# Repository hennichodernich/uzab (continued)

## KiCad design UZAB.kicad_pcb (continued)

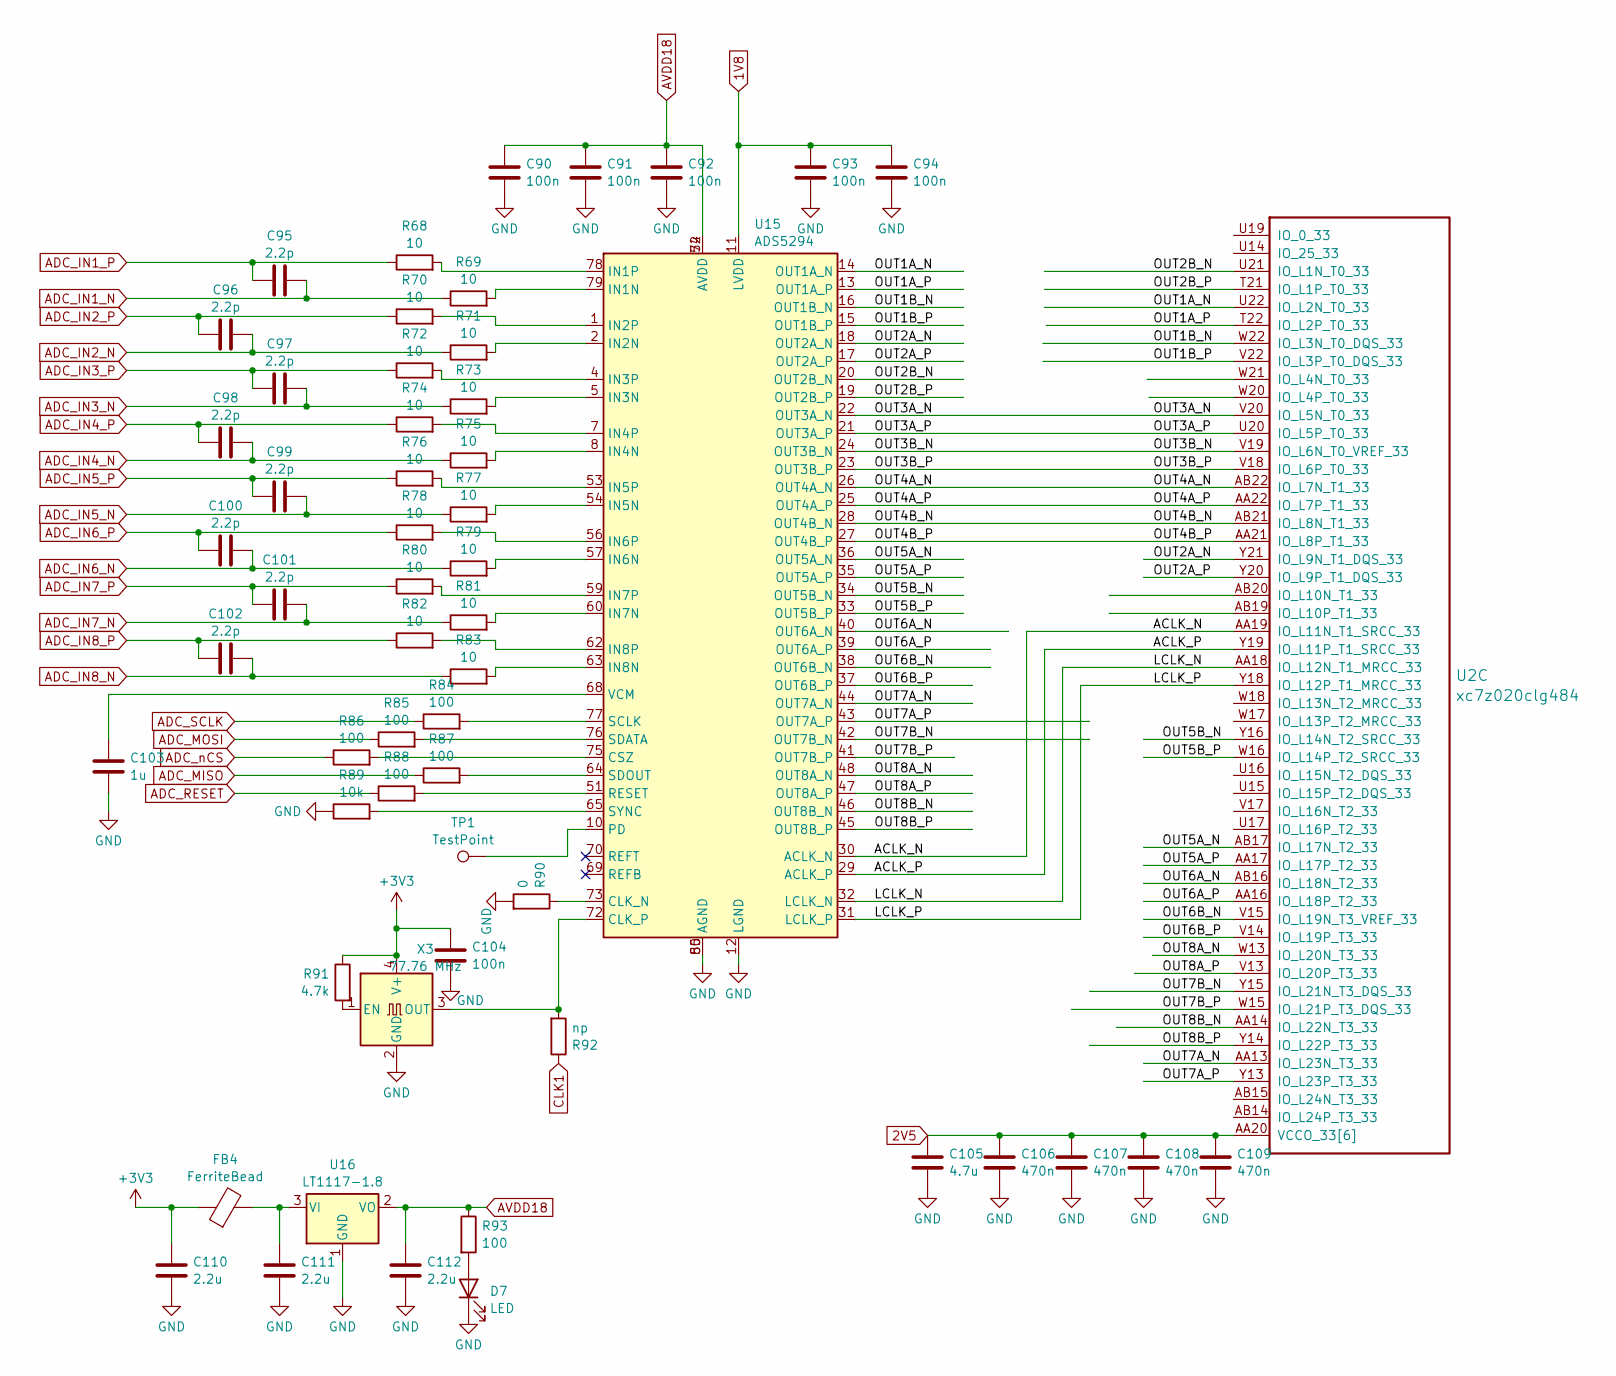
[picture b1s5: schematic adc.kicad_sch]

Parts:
C90, C91, C92, C93, C94, C104: 100n; C_0402_1005Metric
C95, C96, C97, C98, C99, C100, C101, C102: 2.2p; C_0402_1005Metric
C103: 1u; C_0603_1608Metric
C105: 4.7u; C_0603_1608Metric
C106, C107, C108, C109: 470n; C_0201_BGA
C110, C111, C112: 2.2u; C_0603_1608Metric
D7: LED; LED_0603_1608Metric
FB4: FerriteBead; L_0603_1608Metric
R68, R69, R70, R71, R72, R73, R74, R75, R76, R77, R78, R79, R80, R81, R82, R83: 10; R_0402_1005Metric
R84, R85, R86, R87, R88: 100; C_0603_1608Metric
R89: 10k; C_0603_1608Metric
R90: 0; R_0402_1005Metric
R91: 4.7k; R_0402_1005Metric
R92: np; R_0402_1005Metric
R93: 100; R_0603_1608Metric
TP1: TestPoint; TestPoint_Pad_1.0x1.0mm
U2: xc7z020clg484; Xilinx_CLG484_CLG485
U15: ADS5294; HTQFP-80-1EP_12x12mm_P0.5mm_EP10x10mm
U16: LT1117-1.8; SOT-223-3_TabPin2
X3: 77.76 MHz; Oscillator_SMD_EuroQuartz_XO91-4Pin_7.0x5.0mm

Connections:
1V8: C93.1, C94.1, U15.11 (LVDD), U15.49 (LVDD); also elsewhere on the board
2V5: C105.1, C106.1, C107.1, C108.1, C109.1, U2.AA20 (VCCO_33[6]), U2.AB13 (VCCO_33[6]), U2.U18 (VCCO_33[6]), U2.V21 (VCCO_33[6]), U2.W14 (VCCO_33[6]), U2.Y17 (VCCO_33[6]); also elsewhere on the board
3V3: C104.1, C110.1, FB4.1, R91.1, X3.4 (V+); also elsewhere on the board
/ADC/ACLK_N: U2.AA19 (IO_L11N_T1_SRCC_33), U15.30 (ACLK_N)
/ADC/ACLK_P: U2.Y19 (IO_L11P_T1_SRCC_33), U15.29 (ACLK_P)
/ADC/LCLK_N: U2.AA18 (IO_L12N_T1_MRCC_33), U15.32 (LCLK_N)
/ADC/LCLK_P: U2.Y18 (IO_L12P_T1_MRCC_33), U15.31 (LCLK_P)
/ADC/OUT1A_N: U2.U22 (IO_L2N_T0_33), U15.14 (OUT1A_N)
/ADC/OUT1A_P: U2.T22 (IO_L2P_T0_33), U15.13 (OUT1A_P)
/ADC/OUT1B_N: U2.W22 (IO_L3N_T0_DQS_33), U15.16 (OUT1B_N)
/ADC/OUT1B_P: U2.V22 (IO_L3P_T0_DQS_33), U15.15 (OUT1B_P)
/ADC/OUT2A_N: U2.Y21 (IO_L9N_T1_DQS_33), U15.18 (OUT2A_N)
/ADC/OUT2A_P: U2.Y20 (IO_L9P_T1_DQS_33), U15.17 (OUT2A_P)
/ADC/OUT2B_N: U2.U21 (IO_L1N_T0_33), U15.20 (OUT2B_N)
/ADC/OUT2B_P: U2.T21 (IO_L1P_T0_33), U15.19 (OUT2B_P)
/ADC/OUT3A_N: U2.V20 (IO_L5N_T0_33), U15.22 (OUT3A_N)
/ADC/OUT3A_P: U2.U20 (IO_L5P_T0_33), U15.21 (OUT3A_P)
/ADC/OUT3B_N: U2.V19 (IO_L6N_T0_VREF_33), U15.24 (OUT3B_N)
/ADC/OUT3B_P: U2.V18 (IO_L6P_T0_33), U15.23 (OUT3B_P)
/ADC/OUT4A_N: U2.AB22 (IO_L7N_T1_33), U15.26 (OUT4A_N)
/ADC/OUT4A_P: U2.AA22 (IO_L7P_T1_33), U15.25 (OUT4A_P)
/ADC/OUT4B_N: U2.AB21 (IO_L8N_T1_33), U15.28 (OUT4B_N)
/ADC/OUT4B_P: U2.AA21 (IO_L8P_T1_33), U15.27 (OUT4B_P)
/ADC/OUT5A_N: U2.AB17 (IO_L17N_T2_33), U15.36 (OUT5A_N)
/ADC/OUT5A_P: U2.AA17 (IO_L17P_T2_33), U15.35 (OUT5A_P)
/ADC/OUT5B_N: U2.Y16 (IO_L14N_T2_SRCC_33), U15.34 (OUT5B_N)
/ADC/OUT5B_P: U2.W16 (IO_L14P_T2_SRCC_33), U15.33 (OUT5B_P)
/ADC/OUT6A_N: U2.AB16 (IO_L18N_T2_33), U15.40 (OUT6A_N)
/ADC/OUT6A_P: U2.AA16 (IO_L18P_T2_33), U15.39 (OUT6A_P)
/ADC/OUT6B_N: U2.V15 (IO_L19N_T3_VREF_33), U15.38 (OUT6B_N)
/ADC/OUT6B_P: U2.V14 (IO_L19P_T3_33), U15.37 (OUT6B_P)
/ADC/OUT7A_N: U2.AA13 (IO_L23N_T3_33), U15.44 (OUT7A_N)
/ADC/OUT7A_P: U2.Y13 (IO_L23P_T3_33), U15.43 (OUT7A_P)
/ADC/OUT7B_N: U2.Y15 (IO_L21N_T3_DQS_33), U15.42 (OUT7B_N)
/ADC/OUT7B_P: U2.W15 (IO_L21P_T3_DQS_33), U15.41 (OUT7B_P)
/ADC/OUT8A_N: U2.W13 (IO_L20N_T3_33), U15.48 (OUT8A_N)
/ADC/OUT8A_P: U2.V13 (IO_L20P_T3_33), U15.47 (OUT8A_P)
/ADC/OUT8B_N: U2.AA14 (IO_L22N_T3_33), U15.46 (OUT8B_N)
/ADC/OUT8B_P: U2.Y14 (IO_L22P_T3_33), U15.45 (OUT8B_P)
ADC_IN1_N: C95.1, R69.1; also elsewhere on the board
ADC_IN1_P: C95.2, R68.1; also elsewhere on the board
ADC_IN2_N: C96.1, R71.1; also elsewhere on the board
ADC_IN2_P: C96.2, R70.1; also elsewhere on the board
ADC_IN3_N: C97.1, R73.1; also elsewhere on the board
ADC_IN3_P: C97.2, R72.1; also elsewhere on the board
ADC_IN4_N: C98.1, R75.1; also elsewhere on the board
ADC_IN4_P: C98.2, R74.1; also elsewhere on the board
ADC_IN5_N: C99.1, R77.1; also elsewhere on the board
ADC_IN5_P: C99.2, R76.1; also elsewhere on the board
ADC_IN6_N: C100.1, R79.1; also elsewhere on the board
ADC_IN6_P: C100.2, R78.1; also elsewhere on the board
ADC_IN7_N: C101.1, R81.1; also elsewhere on the board
ADC_IN7_P: C101.2, R80.1; also elsewhere on the board
ADC_IN8_N: C102.1, R83.1; also elsewhere on the board
ADC_IN8_P: C102.2, R82.1; also elsewhere on the board
ADC_MISO: R87.1; also elsewhere on the board
ADC_MOSI: R85.1; also elsewhere on the board
ADC_RESET: R88.1; also elsewhere on the board
ADC_SCLK: R84.1; also elsewhere on the board
ADC_nCS: R86.1; also elsewhere on the board
AVDD18: C90.1, C91.1, C92.1, C112.1, R93.1, U15.9 (AVDD), U15.52 (AVDD), U15.66 (AVDD), U15.71 (AVDD), U15.74 (AVDD), U16.2 (VO)
CLK1: R92.1; also elsewhere on the board
GND: C90.2, C91.2, C92.2, C93.2, C94.2, C103.2, C104.2, C105.2, C106.2, C107.2, C108.2, C109.2, C110.2, C111.2, C112.2, D7.1 (K), R89.1, R90.2, U15.3 (AGND), U15.6 (AGND), U15.12 (LGND), U15.50 (LGND), U15.55 (AGND), U15.58 (AGND), U15.61 (AGND), U15.80 (AGND), U15.81 (AGND), U16.1 (GND), X3.2 (GND); also elsewhere on the board
unnamed: D7.2 (A), R93.2
unnamed: R90.1, U15.73 (CLK_N)
unnamed: R92.2, U15.72 (CLK_P), X3.3 (OUT)
unnamed: R86.2, U15.75 (CSZ)
unnamed: R69.2, U15.79 (IN1N)
unnamed: R68.2, U15.78 (IN1P)
unnamed: R71.2, U15.2 (IN2N)
unnamed: R70.2, U15.1 (IN2P)
unnamed: R73.2, U15.5 (IN3N)
unnamed: R72.2, U15.4 (IN3P)
unnamed: R75.2, U15.8 (IN4N)
unnamed: R74.2, U15.7 (IN4P)
unnamed: R77.2, U15.54 (IN5N)
unnamed: R76.2, U15.53 (IN5P)
unnamed: R79.2, U15.57 (IN6N)
unnamed: R78.2, U15.56 (IN6P)
unnamed: R81.2, U15.60 (IN7N)
unnamed: R80.2, U15.59 (IN7P)
unnamed: R83.2, U15.63 (IN8N)
unnamed: R82.2, U15.62 (IN8P)
unnamed: TP1.1, U15.10 (PD)
unnamed: R88.2, U15.51 (RESET)
unnamed: R84.2, U15.77 (SCLK)
unnamed: R85.2, U15.76 (SDATA)
unnamed: R87.2, U15.64 (SDOUT)
unnamed: R89.2, U15.65 (SYNC)
unnamed: C103.1, U15.68 (VCM)
unnamed: C111.1, FB4.2, U16.3 (VI)
unnamed: R91.2, X3.1 (EN)

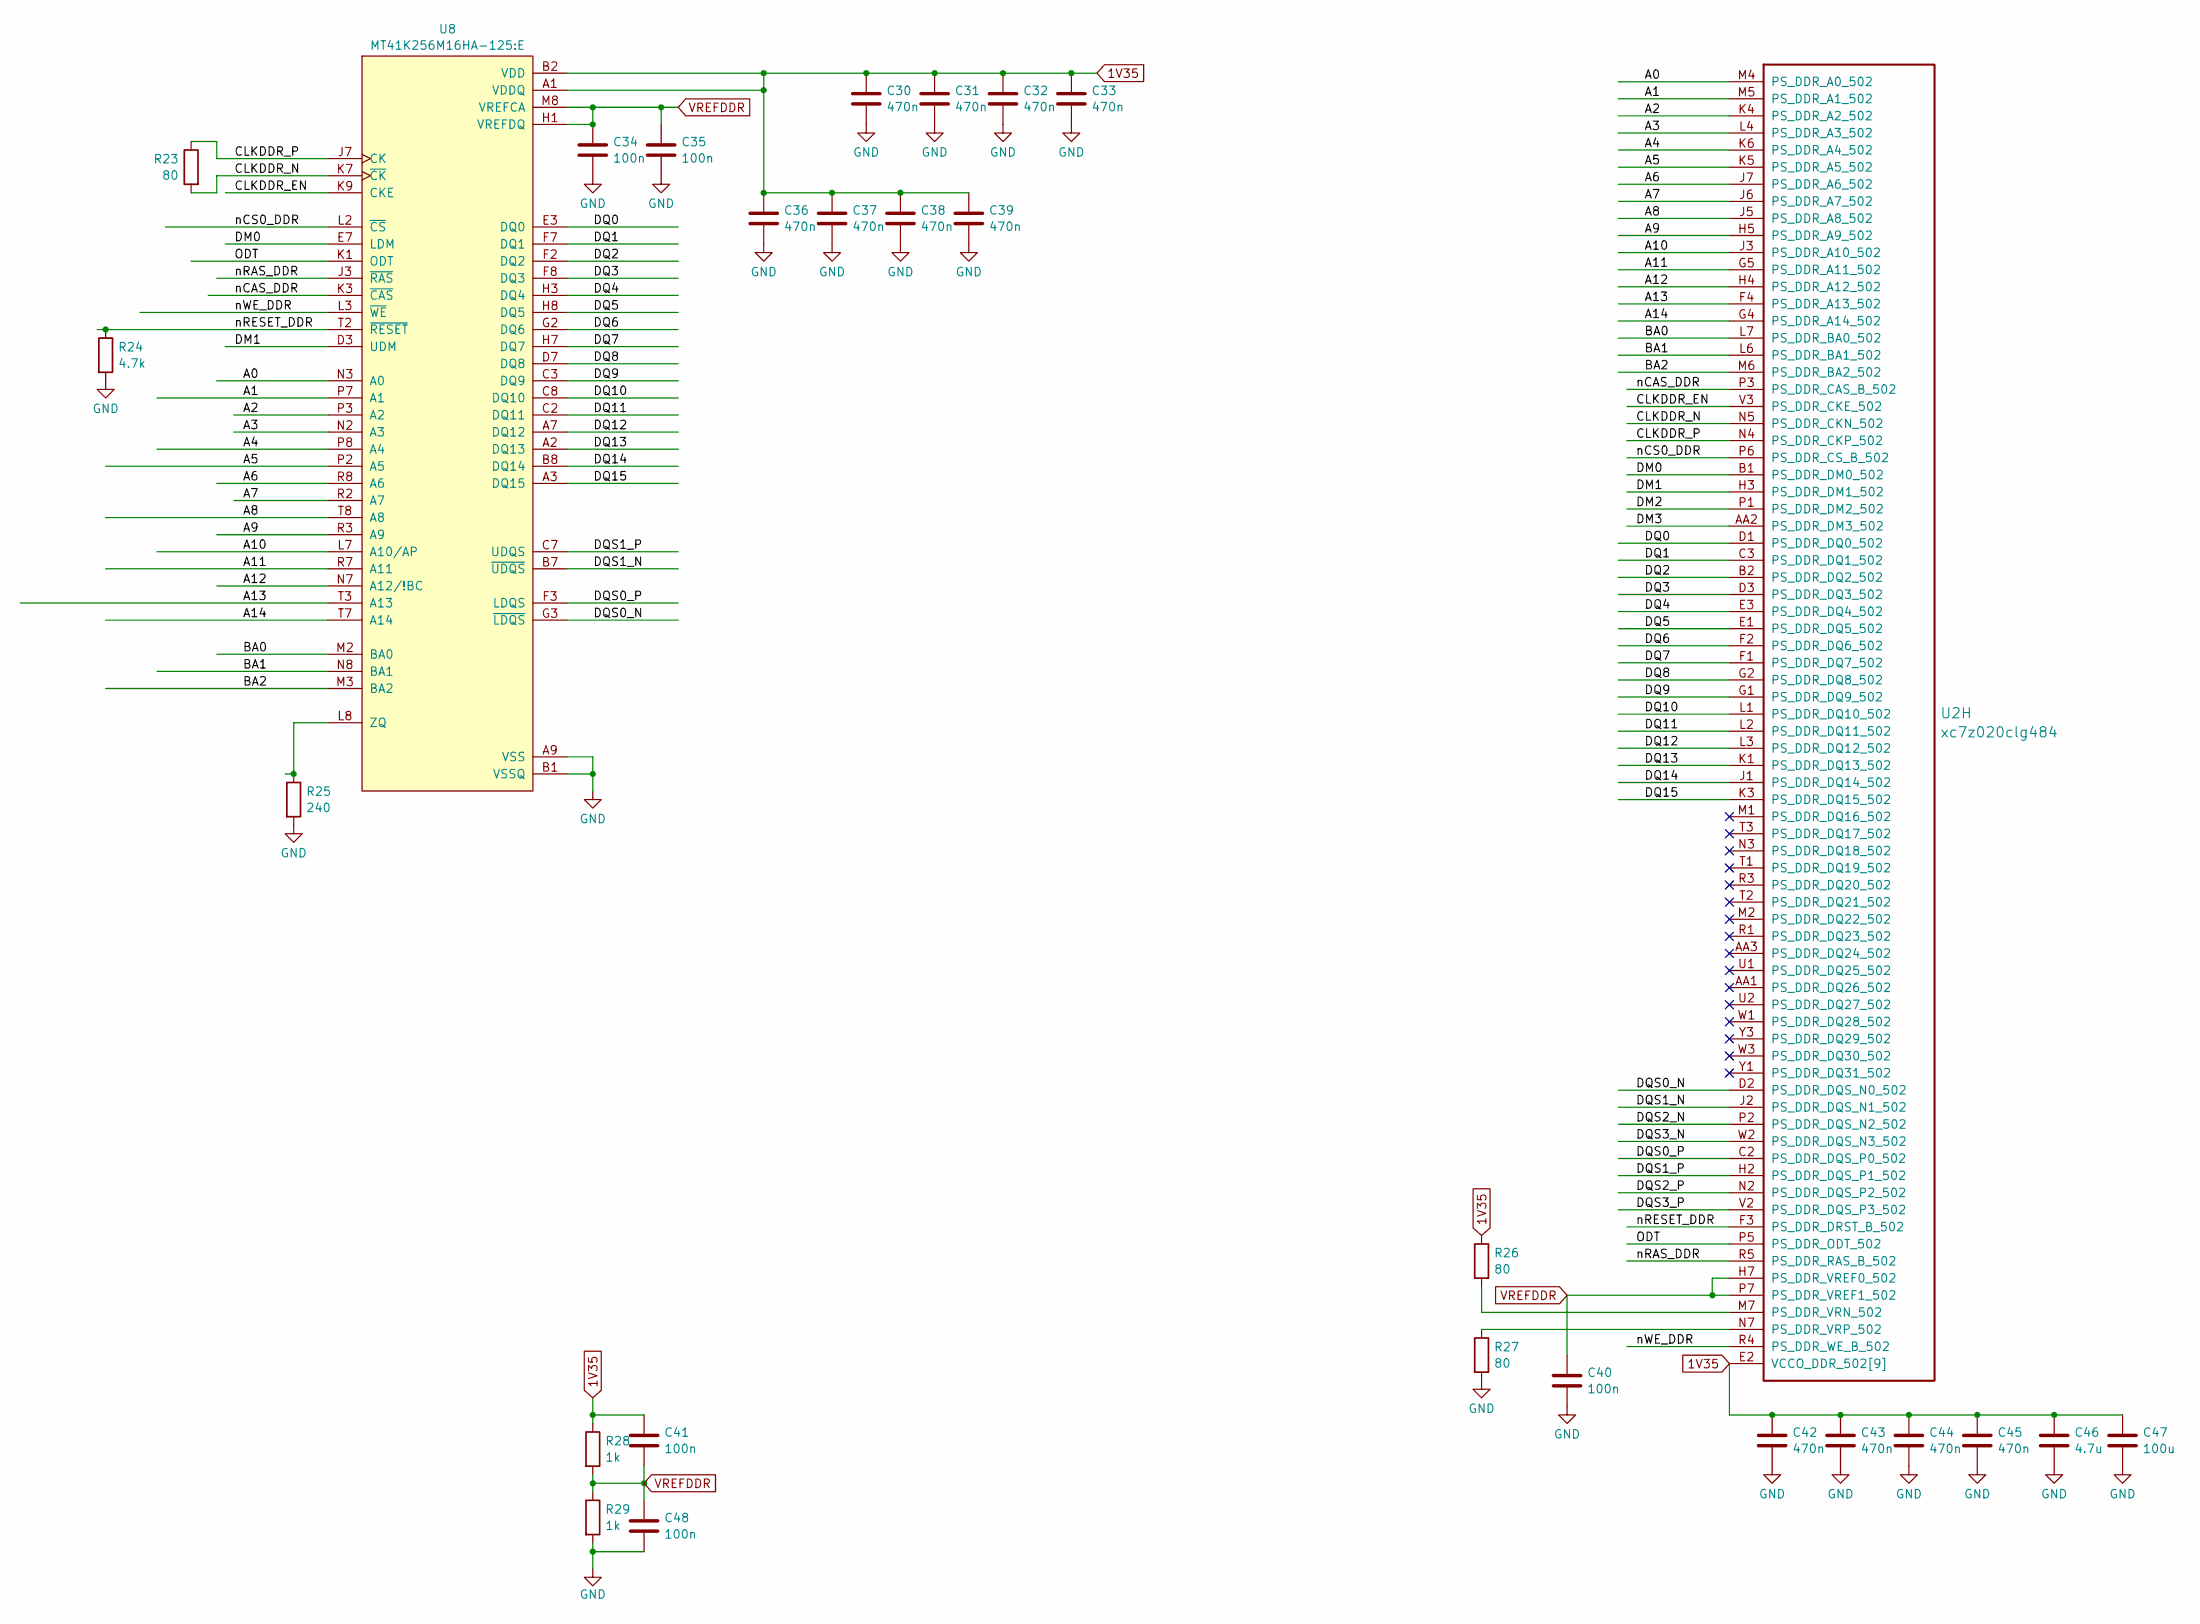
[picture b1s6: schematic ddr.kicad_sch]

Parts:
C30, C31, C32, C33, C36, C37, C38, C39, C45: 470n; C_0402_1005Metric
C34, C35, C41, C48: 100n; C_0402_1005Metric
C40: 100n; C_0201_BGA
C42, C43, C44: 470n; C_0402_BGA
C46: 4.7u; C_0603_1608Metric
C47: 100u; C_1206_3216Metric
R23: 80; C_0402_BGA
R24: 4.7k; R_0402_1005Metric
R25: 240; R_0402_1005Metric
R26: 80; C_0402_BGA_skip1
R27: 80; R_0402_BGA_Diag
R28, R29: 1k; R_0402_1005Metric
U2: xc7z020clg484; Xilinx_CLG484_CLG485
U8: MT41K256M16HA-125:E; Micron_FBGA-96_9x14mm_Layout9x16_P0.8mm_0.45mm_Pads

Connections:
1V35: C30.1, C31.1, C32.1, C33.1, C36.1, C37.1, C38.1, C39.1, C41.1, C42.1, C43.1, C44.1, C45.1, C46.1, C47.1, R26.1, R28.1, U2.E2 (VCCO_DDR_502[9]), U2.F5 (VCCO_DDR_502[9]), U2.H1 (VCCO_DDR_502[9]), U2.J4 (VCCO_DDR_502[9]), U2.K7 (VCCO_DDR_502[9]), U2.M3 (VCCO_DDR_502[9]), U2.N6 (VCCO_DDR_502[9]), U2.R2 (VCCO_DDR_502[9]), U2.V1 (VCCO_DDR_502[9]), U8.A1 (VDDQ), U8.A8 (VDDQ), U8.B2 (VDD), U8.C1 (VDDQ), U8.C9 (VDDQ), U8.D2 (VDDQ), U8.D9 (VDD), U8.E9 (VDDQ), U8.F1 (VDDQ), U8.G7 (VDD), U8.H2 (VDDQ), U8.H9 (VDDQ), U8.K2 (VDD), U8.K8 (VDD), U8.N1 (VDD), U8.N9 (VDD), U8.R1 (VDD), U8.R9 (VDD); also elsewhere on the board
/DDR/A0: U2.M4 (PS_DDR_A0_502), U8.N3 (A0)
/DDR/A1: U2.M5 (PS_DDR_A1_502), U8.P7 (A1)
/DDR/A2: U2.K4 (PS_DDR_A2_502), U8.P3 (A2)
/DDR/A3: U2.L4 (PS_DDR_A3_502), U8.N2 (A3)
/DDR/A4: U2.K6 (PS_DDR_A4_502), U8.P8 (A4)
/DDR/A5: U2.K5 (PS_DDR_A5_502), U8.P2 (A5)
/DDR/A6: U2.J7 (PS_DDR_A6_502), U8.R8 (A6)
/DDR/A7: U2.J6 (PS_DDR_A7_502), U8.R2 (A7)
/DDR/A8: U2.J5 (PS_DDR_A8_502), U8.T8 (A8)
/DDR/A9: U2.H5 (PS_DDR_A9_502), U8.R3 (A9)
/DDR/A10: U2.J3 (PS_DDR_A10_502), U8.L7 (A10/AP)
/DDR/A11: U2.G5 (PS_DDR_A11_502), U8.R7 (A11)
/DDR/A12: U2.H4 (PS_DDR_A12_502), U8.N7 (A12/!BC)
/DDR/A13: U2.F4 (PS_DDR_A13_502), U8.T3 (A13)
/DDR/A14: U2.G4 (PS_DDR_A14_502), U8.T7 (A14)
/DDR/BA0: U2.L7 (PS_DDR_BA0_502), U8.M2 (BA0)
/DDR/BA1: U2.L6 (PS_DDR_BA1_502), U8.N8 (BA1)
/DDR/BA2: U2.M6 (PS_DDR_BA2_502), U8.M3 (BA2)
/DDR/CLKDDR_EN: U2.V3 (PS_DDR_CKE_502), U8.K9 (CKE)
/DDR/CLKDDR_N: R23.2, U2.N5 (PS_DDR_CKN_502), U8.K7 (~CK)
/DDR/CLKDDR_P: R23.1, U2.N4 (PS_DDR_CKP_502), U8.J7 (CK)
/DDR/DM0: U2.B1 (PS_DDR_DM0_502), U8.E7 (LDM)
/DDR/DM1: U2.H3 (PS_DDR_DM1_502), U8.D3 (UDM)
/DDR/DM2: U2.P1 (PS_DDR_DM2_502)
/DDR/DM3: U2.AA2 (PS_DDR_DM3_502)
/DDR/DQ0: U2.D1 (PS_DDR_DQ0_502), U8.E3 (DQ0)
/DDR/DQ1: U2.C3 (PS_DDR_DQ1_502), U8.F7 (DQ1)
/DDR/DQ2: U2.B2 (PS_DDR_DQ2_502), U8.F2 (DQ2)
/DDR/DQ3: U2.D3 (PS_DDR_DQ3_502), U8.F8 (DQ3)
/DDR/DQ4: U2.E3 (PS_DDR_DQ4_502), U8.H3 (DQ4)
/DDR/DQ5: U2.E1 (PS_DDR_DQ5_502), U8.H8 (DQ5)
/DDR/DQ6: U2.F2 (PS_DDR_DQ6_502), U8.G2 (DQ6)
/DDR/DQ7: U2.F1 (PS_DDR_DQ7_502), U8.H7 (DQ7)
/DDR/DQ8: U2.G2 (PS_DDR_DQ8_502), U8.D7 (DQ8)
/DDR/DQ9: U2.G1 (PS_DDR_DQ9_502), U8.C3 (DQ9)
/DDR/DQ10: U2.L1 (PS_DDR_DQ10_502), U8.C8 (DQ10)
/DDR/DQ11: U2.L2 (PS_DDR_DQ11_502), U8.C2 (DQ11)
/DDR/DQ12: U2.L3 (PS_DDR_DQ12_502), U8.A7 (DQ12)
/DDR/DQ13: U2.K1 (PS_DDR_DQ13_502), U8.A2 (DQ13)
/DDR/DQ14: U2.J1 (PS_DDR_DQ14_502), U8.B8 (DQ14)
/DDR/DQ15: U2.K3 (PS_DDR_DQ15_502), U8.A3 (DQ15)
/DDR/DQS0_N: U2.D2 (PS_DDR_DQS_N0_502), U8.G3 (~LDQS)
/DDR/DQS0_P: U2.C2 (PS_DDR_DQS_P0_502), U8.F3 (LDQS)
/DDR/DQS1_N: U2.J2 (PS_DDR_DQS_N1_502), U8.B7 (~UDQS)
/DDR/DQS1_P: U2.H2 (PS_DDR_DQS_P1_502), U8.C7 (UDQS)
/DDR/DQS2_N: U2.P2 (PS_DDR_DQS_N2_502)
/DDR/DQS2_P: U2.N2 (PS_DDR_DQS_P2_502)
/DDR/DQS3_N: U2.W2 (PS_DDR_DQS_N3_502)
/DDR/DQS3_P: U2.V2 (PS_DDR_DQS_P3_502)
/DDR/ODT: U2.P5 (PS_DDR_ODT_502), U8.K1 (ODT)
/DDR/nCAS_DDR: U2.P3 (PS_DDR_CAS_B_502), U8.K3 (~CAS)
/DDR/nCS0_DDR: U2.P6 (PS_DDR_CS_B_502), U8.L2 (~CS)
/DDR/nRAS_DDR: U2.R5 (PS_DDR_RAS_B_502), U8.J3 (~RAS)
/DDR/nRESET_DDR: R24.1, U2.F3 (PS_DDR_DRST_B_502), U8.T2 (~RESET)
/DDR/nWE_DDR: U2.R4 (PS_DDR_WE_B_502), U8.L3 (~WE)
GND: C30.2, C31.2, C32.2, C33.2, C34.2, C35.2, C36.2, C37.2, C38.2, C39.2, C40.2, C42.2, C43.2, C44.2, C45.2, C46.2, C47.2, C48.2, R24.2, R25.2, R27.2, R29.2, U8.A9 (VSS), U8.B1 (VSSQ), U8.B3 (VSS), U8.B9 (VSSQ), U8.D1 (VSSQ), U8.D8 (VSSQ), U8.E1 (VSS), U8.E2 (VSSQ), U8.E8 (VSSQ), U8.F9 (VSSQ), U8.G1 (VSSQ), U8.G8 (VSS), U8.G9 (VSSQ), U8.J2 (VSS), U8.J8 (VSS), U8.M1 (VSS), U8.M9 (VSS), U8.P1 (VSS), U8.P9 (VSS), U8.T1 (VSS), U8.T9 (VSS); also elsewhere on the board
unnamed: R26.2, U2.M7 (PS_DDR_VRN_502)
unnamed: R27.1, U2.N7 (PS_DDR_VRP_502)
unnamed: R25.1, U8.L8 (ZQ)
VREFDDR: C34.1, C35.1, C40.1, C41.2, C48.1, R28.2, R29.1, U2.H7 (PS_DDR_VREF0_502), U2.P7 (PS_DDR_VREF1_502), U8.H1 (VREFDQ), U8.M8 (VREFCA)

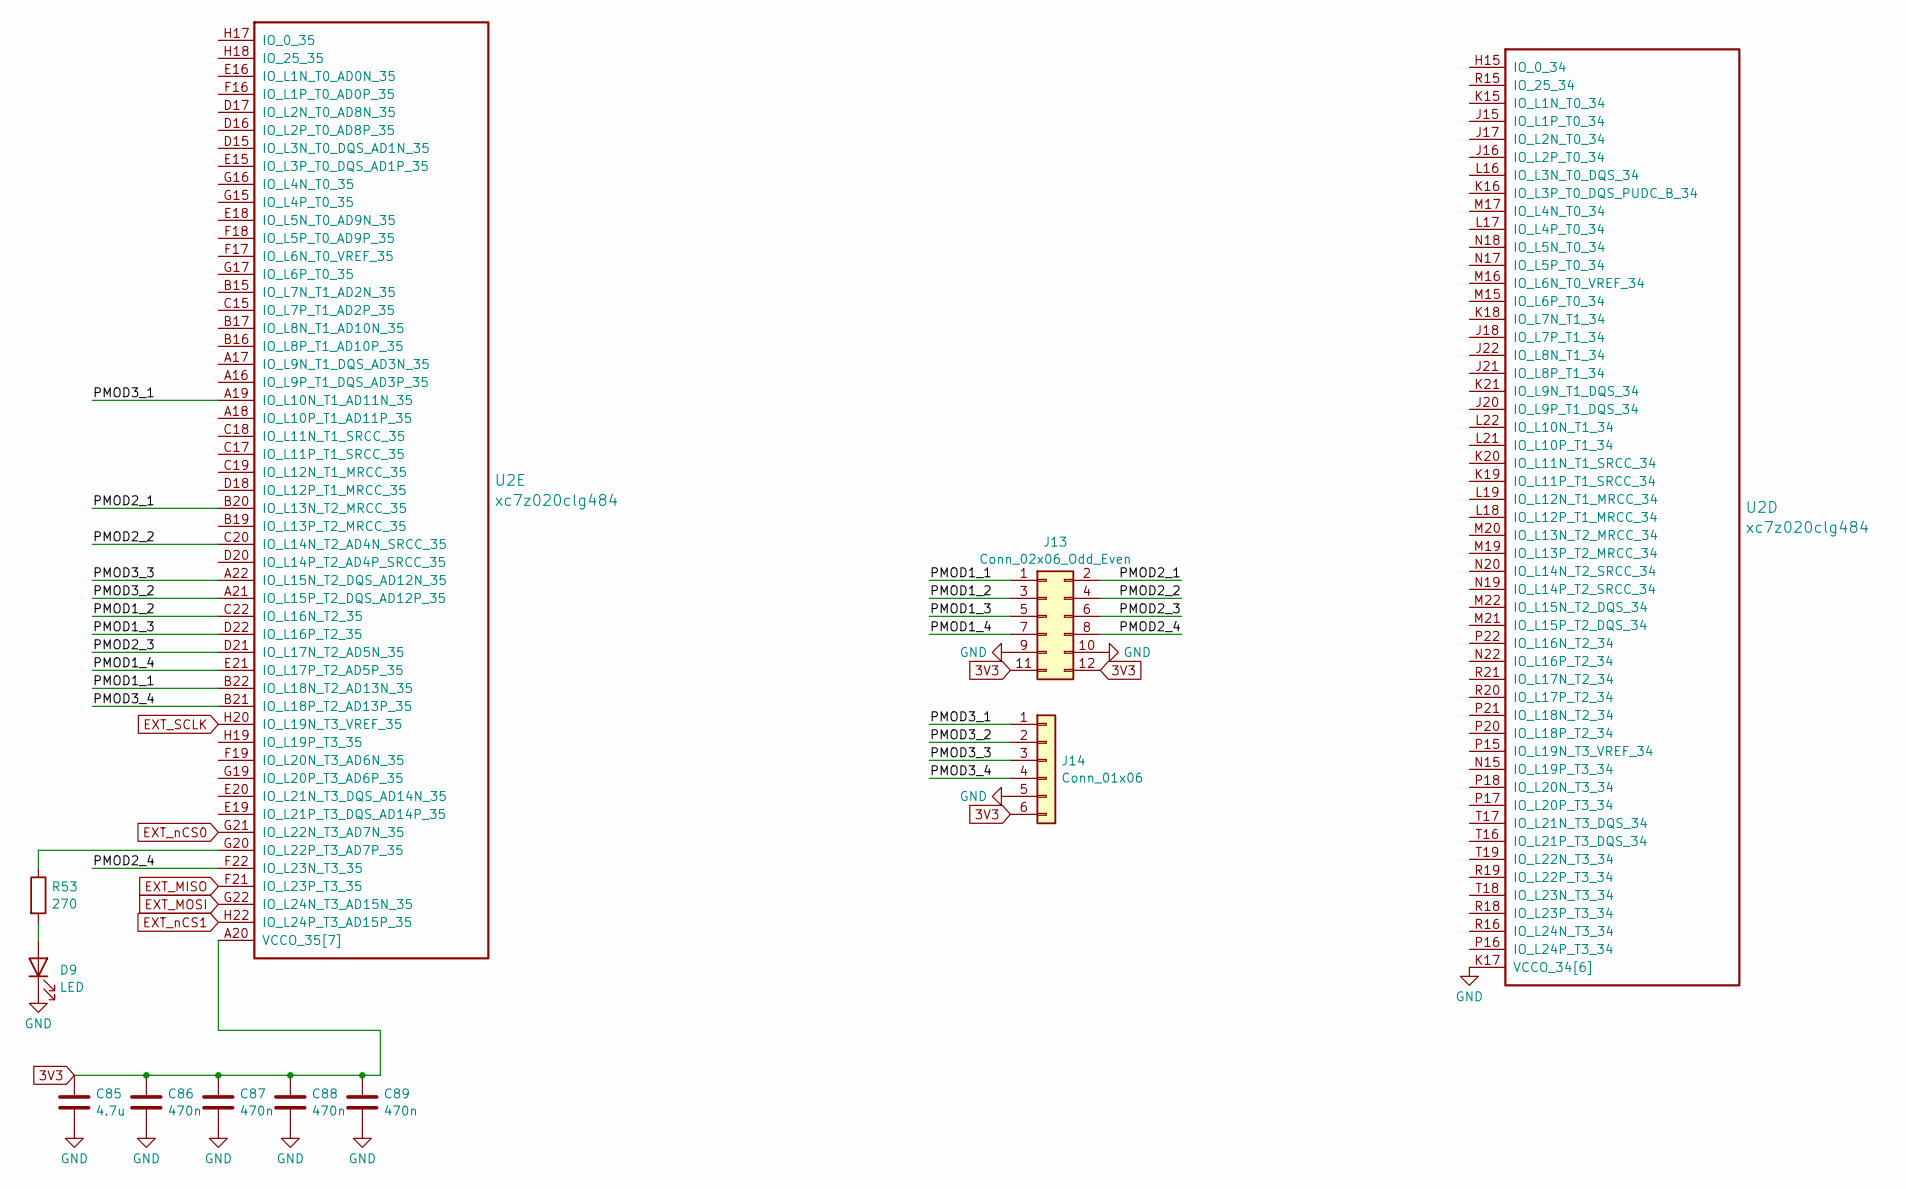
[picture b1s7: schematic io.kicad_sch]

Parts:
C85: 4.7u; C_0603_1608Metric
C86, C87, C88, C89: 470n; C_0201_BGA
D9: LED; LED_0603_1608Metric
J13: Conn_02x06_Odd_Even; PinSocket_2x06_P2.54mm_Vertical
J14: Conn_01x06; PinSocket_1x06_P2.54mm_Vertical
R53: 270; R_0402_1005Metric
U2: xc7z020clg484; Xilinx_CLG484_CLG485

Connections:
3V3: C85.1, C86.1, C87.1, C88.1, C89.1, J13.11, J13.12, J14.6, U2.A20 (VCCO_35[7]), U2.C16 (VCCO_35[7]), U2.D19 (VCCO_35[7]), U2.E22 (VCCO_35[7]), U2.F15 (VCCO_35[7]), U2.G18 (VCCO_35[7]), U2.H21 (VCCO_35[7]); also elsewhere on the board
/IO/PMOD1_1: J13.1, U2.B22 (IO_L18N_T2_AD13N_35)
/IO/PMOD1_2: J13.3, U2.C22 (IO_L16N_T2_35)
/IO/PMOD1_3: J13.5, U2.D22 (IO_L16P_T2_35)
/IO/PMOD1_4: J13.7, U2.E21 (IO_L17P_T2_AD5P_35)
/IO/PMOD2_1: J13.2, U2.B20 (IO_L13N_T2_MRCC_35)
/IO/PMOD2_2: J13.4, U2.C20 (IO_L14N_T2_AD4N_SRCC_35)
/IO/PMOD2_3: J13.6, U2.D21 (IO_L17N_T2_AD5N_35)
/IO/PMOD2_4: J13.8, U2.F22 (IO_L23N_T3_35)
/IO/PMOD3_1: J14.1, U2.A19 (IO_L10N_T1_AD11N_35)
/IO/PMOD3_2: J14.2, U2.A21 (IO_L15P_T2_DQS_AD12P_35)
/IO/PMOD3_3: J14.3, U2.A22 (IO_L15N_T2_DQS_AD12N_35)
/IO/PMOD3_4: J14.4, U2.B21 (IO_L18P_T2_AD13P_35)
EXT_MISO: U2.F21 (IO_L23P_T3_35); also elsewhere on the board
EXT_MOSI: U2.G22 (IO_L24N_T3_AD15N_35); also elsewhere on the board
EXT_SCLK: U2.H20 (IO_L19N_T3_VREF_35); also elsewhere on the board
EXT_nCS0: U2.G21 (IO_L22N_T3_AD7N_35); also elsewhere on the board
EXT_nCS1: U2.H22 (IO_L24P_T3_AD15P_35); also elsewhere on the board
GND: C85.2, C86.2, C87.2, C88.2, C89.2, D9.1 (K), J13.9, J13.10, J14.5, U2.K17 (VCCO_34[6]), U2.L20 (VCCO_34[6]), U2.N16 (VCCO_34[6]), U2.P19 (VCCO_34[6]), U2.R22 (VCCO_34[6]), U2.T15 (VCCO_34[6]); also elsewhere on the board
unnamed: D9.2 (A), R53.2
unnamed: R53.1, U2.G20 (IO_L22P_T3_AD7P_35)

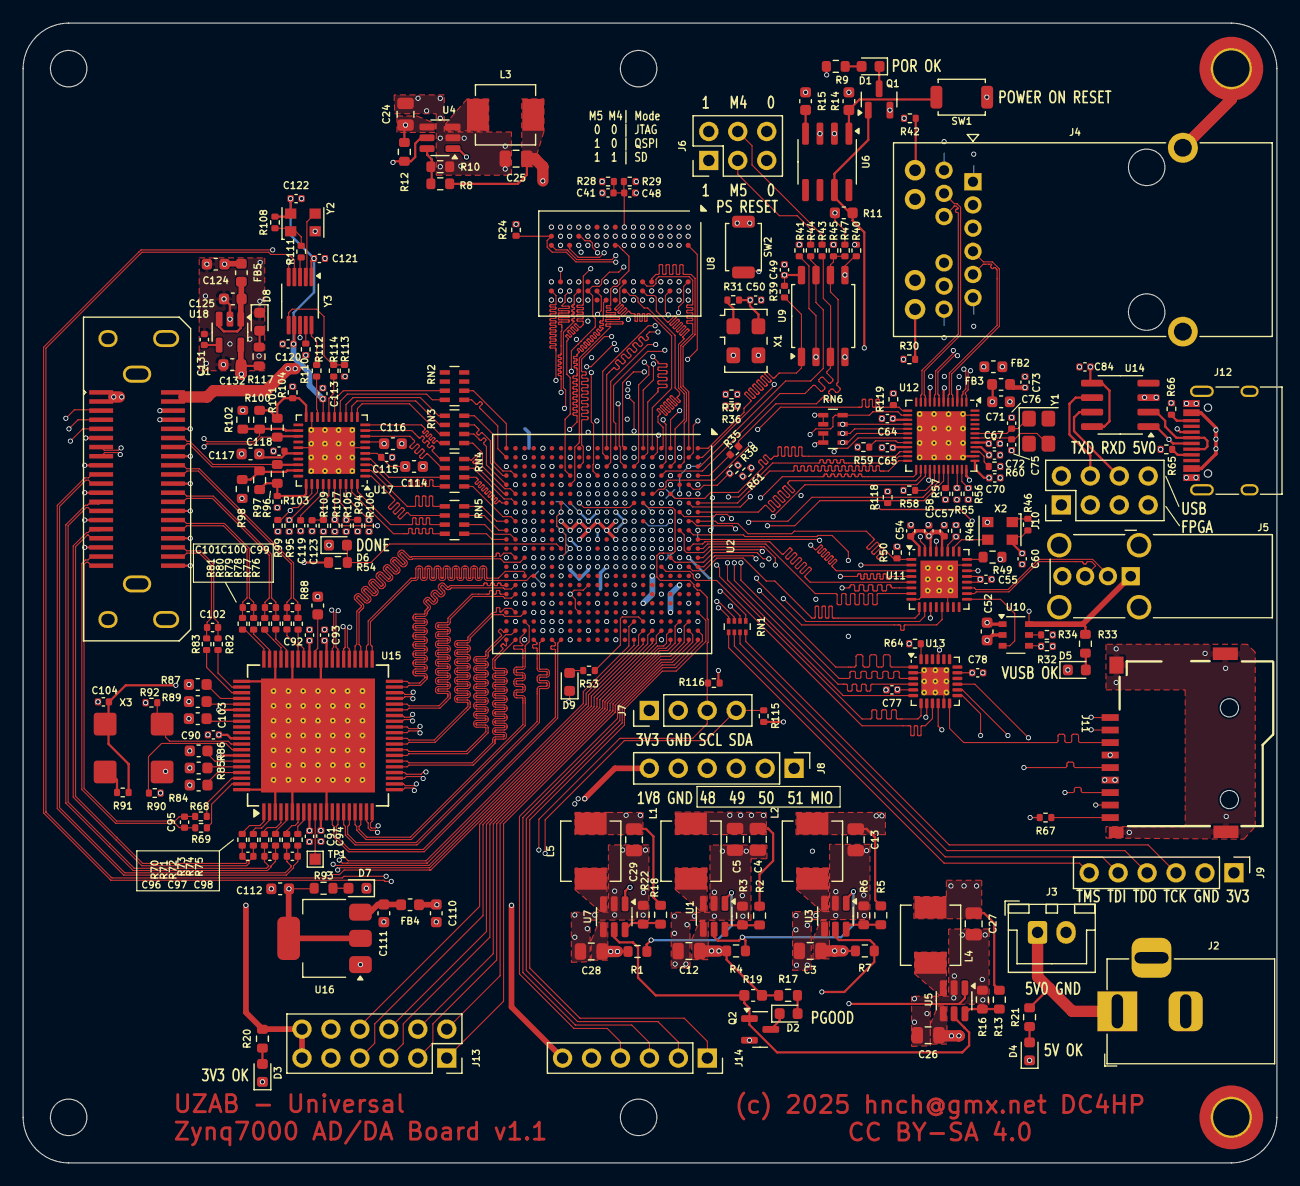
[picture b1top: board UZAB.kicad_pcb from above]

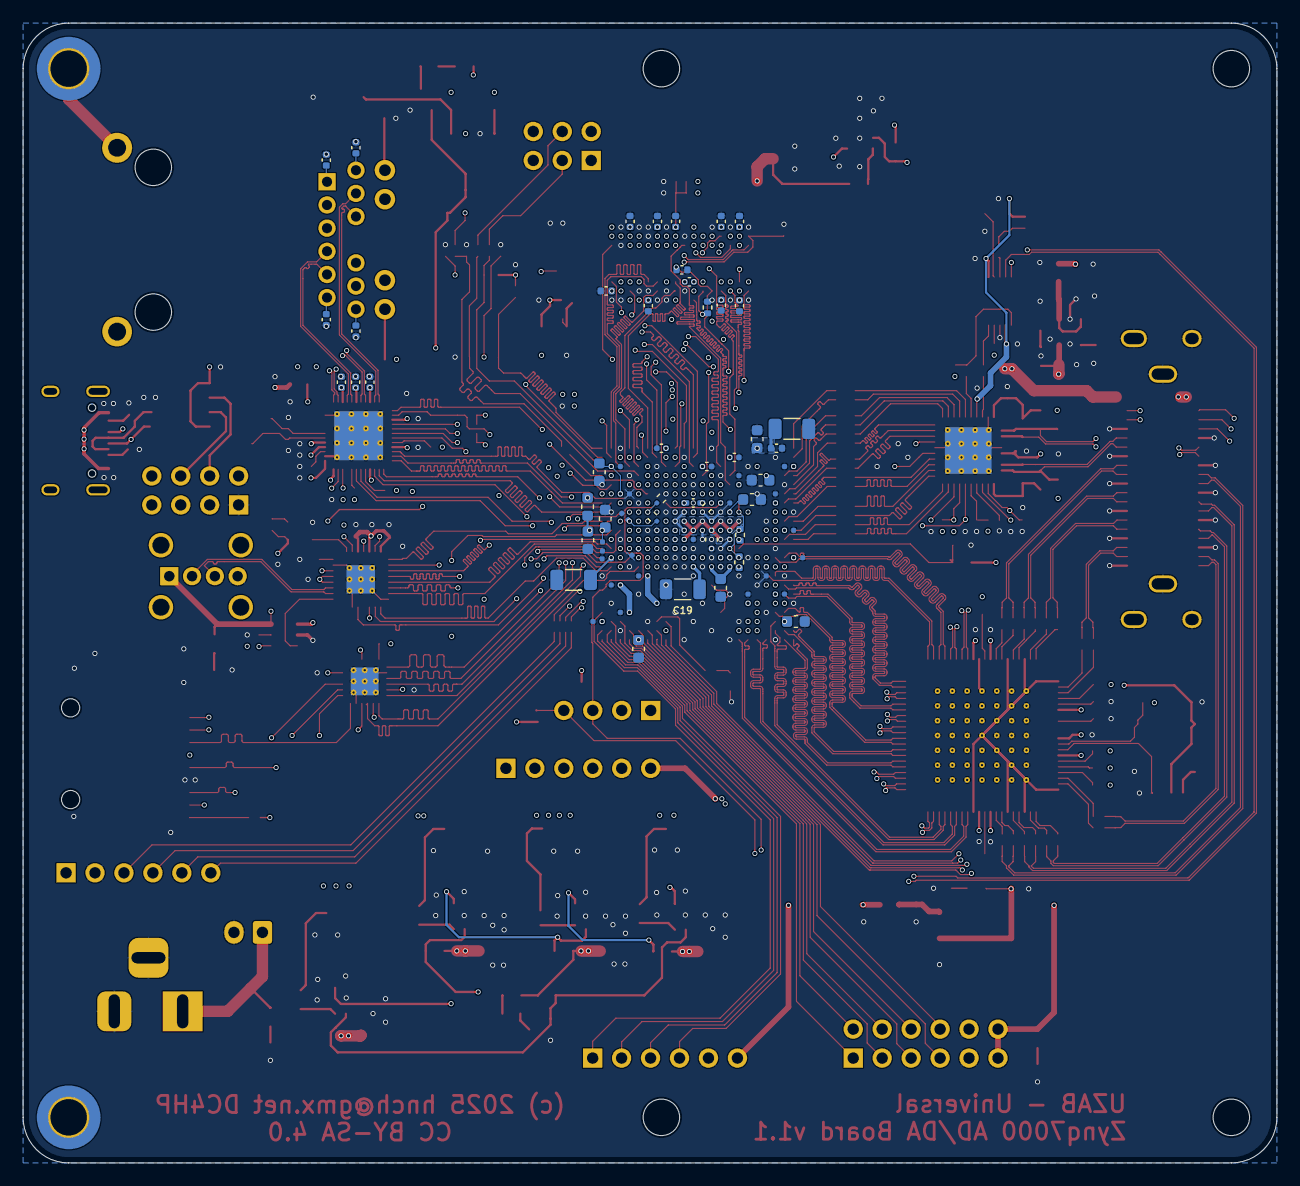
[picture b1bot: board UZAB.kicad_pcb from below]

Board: 6 copper layers, 110.0 x 100.0 mm, 325 parts (75 on the bottom side), 362 nets.
